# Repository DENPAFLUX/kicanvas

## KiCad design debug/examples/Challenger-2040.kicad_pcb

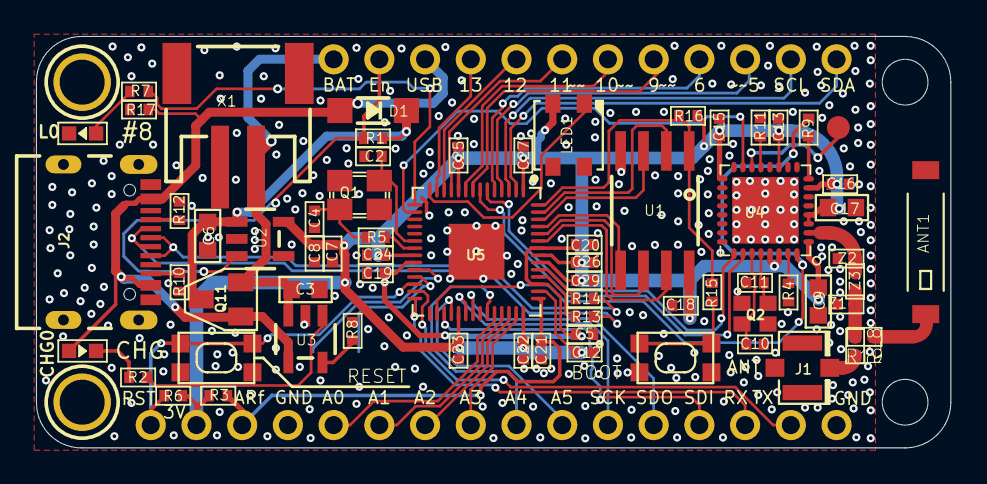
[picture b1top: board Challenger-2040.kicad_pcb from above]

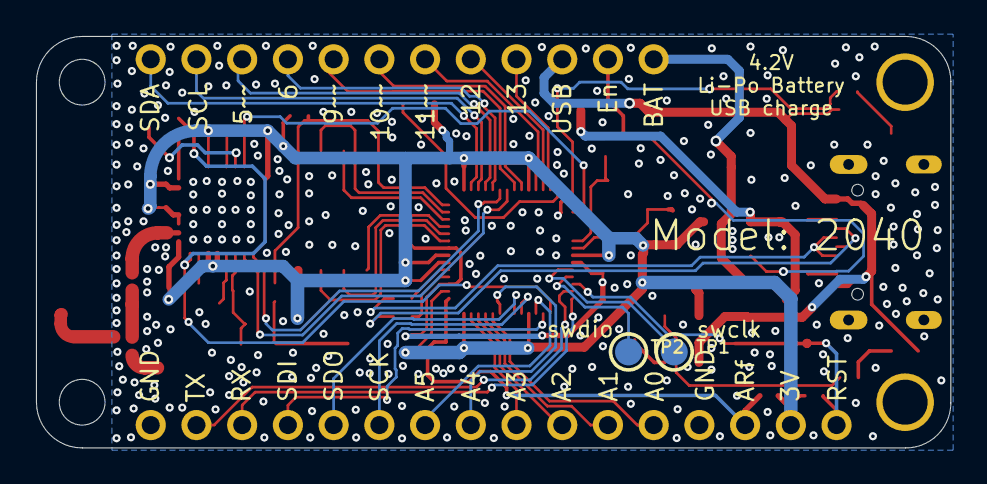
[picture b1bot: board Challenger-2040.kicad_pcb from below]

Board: 2 copper layers, 50.8 x 22.9 mm, 77 parts (4 on the bottom side), 67 nets.

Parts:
ANT1: ACAG0801-2450-T; ANTENNA-CHIP6
C2, C4: 12pF; CAPC1005X60_22219331
C3, C6, C9, C17: 10uF; CAPC1608X85_22219331
C5, C12: 1uF; CAPC1005X60_22219331
C7, C13, C15, C16, C18, C19, C20, C22, C23, C24, C25, C26, C27, C29: 0.1uF; CAPC1005X60_22219331
C8: 4.7uF; CAPC1005X60_22219331
C10, C11: 8.2pF; CAPC1005X60_22219331
C21: 2.2uF; CAPC1005X60_22219331
CHG0: RED; CHIPLED_0603_18621472
D1: MBR120; SOD-123_30573741
J1: U.FL; U.FL_29785348
J2: USB4105-GF-A; GCT_USB4105-GF-A_21150292
JP1: 1X16_ROUND
JP3: 1X12_ROUND
L0: GREEN; CHIPLED_0603_18621472
LED1: SK6812MINI-B; LED3535
LOGO1: CHALENGER-11MM; CHALLENGER_21548800
Q1: 12MHz; NX3225
Q2: 26MHz; FA-128_204
Q11: SL3401A-TP; SUPER-SOT3
R1, R17: 100K; RESC1005X40_22219245
R2: 560R; RESC1005X40_22219245
R3, R18, R19: 0R; RESC1005X40_22219245
R4, R11: 12K; RESC1005X40_22219245
R5, R9, R15: 1K; RESC1005X40_22219245
R6, R16: 10K; RESC1005X40_22219245
R7: 330R; RESC1005X40_22219245
R8: 2K; RESC1005X40_22219245
R10, R12: 5K1; RESC1005X40_22219245
R13, R14: 27R; RESC1005X40_22219245
SW1, SW2: SPST_TACT-KMR2; KMR2
TP1, TP2: TESTPOINT_ROUND_1.5MM
TP3: TPB1,27; B1,27_385
U1: W25Q64; SOIC8_208MIL
U2: AP2112K-3.3TRG; SOT23-5
U3: MCP73831T-2ACI/OT; SOT23-5
U4: ESP8285; SLP32
U5: RP2040; QFN40P700X700X90-57T310N_29136831
U$11: CHAL-TEXT; CHAL-TEXT_21548800
U$31, U$32: MOUNTINGHOLE2.5; MOUNTINGHOLE_2.5_PLATED
UNK_HOLE_0: dummyfp0
UNK_HOLE_1: dummyfp1
X1: JSTPH; JSTPH2
Z1: 2.4pF; CAPC1005X60_22219331
Z2: 2.7pF; CAPC1005X60_22219331
Z3: 2.6nH; CAPC1005X60_22219331

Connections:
+3V3: C7.1, C8.1, C9.2, C12.2, C13.1, C15.1, C16.1, C17.1, C18.1, C22.2, C23.2, C24.2, C25.2, C26.2, C27.2, C29.2, JP1.15, LED1.2, R3.2, R6.2, R16.1, U1.8, U2.5, U4.1, U4.3, U4.4, U4.7, U4.11, U4.17, U4.29, U4.30, U5.1, U5.10, U5.22, U5.33, U5.42, U5.44, U5.48, U5.49
A0: JP1.12, U5.38
A1: JP1.11, U5.39
A2: JP1.10, U5.40
A3: JP1.9, U5.41
A4: JP1.8, U5.37
AREF: C21.2, JP1.14, R3.1, U5.43
D5: JP3.10, U5.4
D6: JP3.9, U5.5
D9: JP3.8, U5.8
D10: JP3.7, U5.9
D11: JP3.6, U5.11
D12: JP3.5, U5.12
D13: JP3.4, U5.13
D+: J2.A6, J2.B6, R14.1
D-: J2.A7, J2.B7, R13.1
EN: JP3.2, R1.2, U2.3
GND: C2.2, C3.2, C4.2, C5.1, C6.2, C7.2, C8.2, C9.1, C10.2, C11.2, C12.1, C13.2, C15.2, C16.2, C17.2, C18.2, C19.1, C20.1, C21.1, C22.1, C23.1, C24.1, C25.1, C26.1, C27.1, C29.1, J1.P$1, J1.P$2, J1.P$4, J2.A1/B12, J2.B1/A12, J2.G1, J2.G2, J2.G3, J2.G4, JP1.1, JP1.13, L0.C, LED1.4, Q1.2, Q1.4, Q2.2, Q2.4, R4.2, R8.2, R10.2, R11.2, R12.1, R17.2, SW1.2, SW1.4, SW2.2, SW2.4, U1.4, U2.2, U3.2, U4.33, U5.19, U5.57, X1.1, Z1.1, Z2.1
I2C0_SCL: JP3.11, U5.3
I2C0_SDA: JP3.12, U5.2
LED: R7.1, U5.15
unnamed: CHG0.C, R2.1
unnamed: L0.A, R7.2
unnamed: R2.2, U3.1
unnamed: R8.1, U3.5
unnamed: R13.2, U5.46
unnamed: R4.1, U4.31
unnamed: R14.2, U5.47
unnamed: C10.1, Q2.1, U4.27
unnamed: TP3.TP, U4.14
unnamed: C11.1, Q2.3, U4.28
unnamed: J2.B5, R10.1
unnamed: J2.A5, R12.2
unnamed: C2.1, Q1.3, U5.20
unnamed: TP1.P$1, U5.24
unnamed: TP2.P$1, U5.25
unnamed: C4.1, Q1.1, R5.2
unnamed: R5.1, U5.21
unnamed: C5.2, C19.2, C20.2, U5.23, U5.45, U5.50
unnamed: J1.P$3, R18.2
unnamed: C6.1, D1.C, Q11.3, R1.1, U2.1
unnamed: ANT1.1, R19.1
unnamed: R11.1, U4.13
NEOPIXEL: LED1.1, U5.14
QSPI_SCLK: U1.6, U5.52
QSPI_SD0: U1.5, U5.53
QSPI_SD1: U1.2, U5.55
QSPI_SD2: U1.3, U5.54
QSPI_SD3: U1.7, U5.51
RF1: U4.2, Z2.2, Z3.2
RF2: R18.1, R19.2, Z1.2, Z3.1
RP2040_RXD: U4.26, U5.7
RP2040_TXD: U4.25, U5.6
RX: JP1.3, U5.28
SCK: JP1.6, U5.34
SDI: JP1.4, U5.31
SDO: JP1.5, U5.35
SLEEP: R9.2, U4.8
TX: JP1.2, U5.27
VBAT: C3.1, JP3.1, Q11.2, U3.3, X1.2
VBUS: CHG0.A, D1.A, J2.A4/B9, J2.B4/A9, JP3.3, Q11.1, R17.1, U3.4
WIFI_BOOT: U4.15, U5.16
~BOOTSEL: R15.2, SW2.1, SW2.3
~CS: JP1.7, U5.32
~QSPI_CS: R15.1, R16.2, U1.1, U5.56
~RESET: JP1.16, R6.1, SW1.1, SW1.3, U5.26
~W_RST: R9.1, U4.32, U5.30

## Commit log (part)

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2026-05-11 feat: add interactive net/wire/label selection to schematic viewer
    - Register Wire, Bus, BusEntry on LayerNames.interactive so they are
    hit-testable on click; paint a thicker invisible bbox on that layer
    - Register NetLabel, GlobalLabel, HierarchicalLabel (via LabelPainter)
    on LayerNames.interactive with a bbox outline for hit-testing
    - Extend SchematicViewer.select() to accept and resolve Wire, Bus,
    NetLabel, GlobalLabel, HierarchicalLabel items via their bboxes
2026-05-11 feat: net highlight with flood-fill connectivity and layer dimming
    When a net item is selected in the schematic viewer:
    - Dim all non-wire/label layers to 25% alpha via the layer highlight system
    - Flood-fill all connected wires/buses from matching label positions using
    endpoint proximity (no full netlist solver needed for visual accuracy)
    - Draw all matching labels and connected wires in KiCad cyan (#00d0ff)
    on the overlay layer using composite 'overlay' blending
2026-05-20 Fix ProjectPage load path for hierarchical data + add Challenger-2040 multi-page example files
